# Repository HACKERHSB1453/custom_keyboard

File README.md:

# my-kkeb

A 113-key modular mechanical keyboard, split into 5 boards that connect with magnetic pogo pins. It is designed in KiCad (PCB) and Fusion (case) for Hack Club's KEEB program.

## Why I built it
I build this because I was interested in split keyboard. I really like how they look but I dont like how they sacrifice a lot of keys and thats makes them difficult to use for some things. So I had the idea to make a modular split keyboard. 
## How it works
The way it works it pretty simple. A pi pico powers it all. I used mcp23017 chips so I could get enough pins for all the matrix rows and colums from just transfering 4 pins thought the modules.
## Repository layout

```
my-kkeb/                 KiCad project (schematics + PCB)
  CUSTOM.pretty/         custom footprints (pogo connector, hot-swap socket, USB-C)
  export/fab/            Gerber zips, one per board, ready for JLCPCB
case/
  <Module>/Case_*.step   case for each module (one body per file for printing)
  <Module>/Plate_*.step  switch plate for each module
  my-kkeb-case-assembly.step   everything together, for viewing only
```

## Building it

1. **PCBs:** upload each zip from `my-kkeb/export/fab/` to JLCPCB as a separate order (5 boards).
2. **Case:** print the `Case_*` and `Plate_*` files from `case/`. I plan to use JLC3DP in black resin.
3. **Parts:** see `bom.csv`
4. **Firmware:** not done yet

## What I learned
I learned a lot of stuff. I learn a lot about how keyboard work. What I think that is the most valuable thing about what I learned is the knowladge about PCBs, I knew some stuff but I have never tried to actually make a PCB before. And it was actually harder than I thought for some things. But overall I enjoyed a lot doing everything. Making the case was definetely harder than doing the PCB, because I didnt really know how to make the it at first. I tried using FreeCad at first since fusion wasnt in linux, and I didnt liked onshape. But I ended up intalling fusion in my windows and Did 95% of they case there and a did some changed on freecad late on.

## Build journal

**Total: 80 hours**

| Date | Hours | What I worked on |
|---|---|---|
| August 3 | 1 h | Research |
| August 4 | – | GitHub repo |
| August 14 | 2 h 50 min | Planning and first 3D model |
| August 15 | 8 h 40 min | Main model, planning, OLED, pogo pins, MCP23017 |
| August 16 | 3 h | PCB |
| August 17 | 3 h 30 min | PCB |
| August 18 | 2 h | Model changes, PCB |
| August 19 | 9 h | Schematic, ERC |
| August 20 | 7 h | PCB placement |
| August 21 | 16 h | PCB placement and wiring |
| August 23 | 4 h | Wiring |
| August 28 | 6 h | Case |
| September 13 | 7 h | Case, rewiring |
| September 20 | 3 h | Case |
| September 25 | 7 h | Case |

### August 3 (1 h)
I have been searching about how keayboards work. And how matrix system works. Spend a total of 1 hour investigating and watching videos about how to keyboards work and how to create one. Here are the links:
- https://www.youtube.com/watch?v=8WXpGTIbxlQ
- https://www.youtube.com/watch?v=7LyziNdFlew
- https://www.youtube.com/watch?v=h-NM1xSSzHQ

### August 4
I created the github repo.

### August 14 (2 h 50 min)
- **2:10AM-3AM:** Planning my keyboard.
- **10PM-12AM:** I kept planning and making a 3D model to get an idea about how the keyboard should look like.

### August 15 (8 h 40 min)
- **12AM-3AM:** I finished the main model.

- **3AM-4:40AM:** I tought that I could add more things so I made the keyboard bigger. And also added attachable parts.

- **4:40AM-6AM:** I planned where everything will go. Searched about how to make the keyboard hotswappable. I had a problem and it is that the keyboard has 96 keys and 2 knobs. The pi pico doesnt have enough pins. I had two main options, use 2 pi picos or use a another chip. But after inverstigating I found ot a way to make it work with a single pi pico.
- **2PM-4PM:** I added an oled screen, installed kicad. And also searched about ways to connect the keyboard with magnets. I found out about pogo pins. And I decided using them.
- **11:20PM-12AM:** I searched about encoreds and searched about how a MCP23017 works and how to use it. I also watched this video about it

### August 16 (3 h)
- **12:20AM-1:50AM:** I created the kicad project and started adding the base thing like the swithes and the pi pico
- **8PM-11PM:** I started designing the pcb.
  - **8:15PM-9PM:** At this point i had the matrix of the right and left part, but it wasnt wired yet.

### August 17 (3 h 30 min)
- **12:30AM-1:40AM:** kept drawing the switch matrix: D30-D58 and their switches
- **3:20AM-3:50AM:** moved the whole matrix out of the main sheet into its own sheet called `left_part` and started using hierarchical schematic since it was for my case. I couldnt find much info online, but I managed to make it work
- **7:30PM-11PM:** I continued with the PCB, I accidentally forgot to save the right part the day before and had to redo that. I also started organizsing thingsa and connect the two main parts. I also search about mousebites. And I decided to use it since the keybaord will be split in multiple parts.

### August 18 (2 h)
- **4AM-4:10AM:** split `left_part` into two sheets, **Left** and **Right** (60 symbols each), and made an empty numpad sheet
- **2:30PM-3:30PM:** I made some changes to the keyboard model.

- **3PM-3:50PM:** filled the **Numpad** sheet: switches, diodes D59-D80 and its connector J3. Added SW2 to the Left sheet
- **11PM-12AM:** I continued with the pcb

### August 19 (9 h)
- **12AM-3AM:** I kept doing the pcb, and finished the connections. I tried to use schematic hiererchy to organize it all. I hope I didnt mess it up. In this period I basically added the Macro pad and the git pad. Here are some photos:
  - **12AM-1AM:** made the **Macro_pad** sheet (diodes D81-D96, connectors J5, J7, J8) and an empty Git_pad sheet
  - **2:25AM-3AM:** filled the **Git_pad** sheet (diodes D97-D112, connector J9)

- **3AM-7AM:** I fixed all the errors that didnt let me start the design of the PCB
  - **4:45AM-6:35AM:** first time the schematic was sent to the PCB editor: **247 footprints** appeared on the board. Replaced the old J1/J2 connectors with the two USB-C ports (J5 and J11)
- **10PM-12AM:** I run the ERC and got 74 errors. And I spend the time fixing them.
  - **11PM-11:40PM:** added labels on the Git_pad, Macro_pad, Numpad and Right sheets (the ERC fixing)

### August 20 (7 h)
- **12AM-5AM:** I started designing the PCB completed positioning the two main parts of the keybaord and also added the diodes to the left half. Here is a photo:
  - **12:45AM-4:50AM:** placed all 112 switches and the first 29 diodes on the Left board, and moved 31 parts to the back side. Removed an extra connector (J10)

- **10PM-12AM:** I continued with the PCB placement
  - **11PM-2:40AM:** placed all 112 diodes, the rest of the switches, the chips and the connectors (246 parts moved). Added the 113th key (MX113 and D113) to the Numpad

*(Postdata: I messed up really bad here, because I thought that the kailh sockets had to go on the front of the plate, I had to fix that late one)*

### August 21 (16 h)
- **12AM-5AM:** I finished the placement of the compenents in the PCB
- **10PM-12AM:** I continued started wiring the components
- **12AM-9AM:** I finished the wiring of the right part, left part. And the numpad.
  - **4:20AM-5:50AM:** first wiring: 553 track pieces and 87 vias
  - **7:15AM-9AM:** kept wigin and got up to **1,987 track pieces and 247 vias**

### August 23 (4 h)
- **12AM-4AM:** I finished wiring all the keybaord.
  - **1:20AM-5AM:** kept wiring and got from 1,987 to 2,514 track pieces, 324 vias
- **7:45PM-8:10PM:** restored a backup from KiCad's history, then kept wiring
- **9:45PM-10:30PM:** more wiring, up to **2,798 track pieces and 361 vias**

### August 24
- **2:30AM-3:30AM:** I added some ressistors and capacitators.

### August 28 (6 h)
- **12AM-6AM:** I started designing the case

### August 31
- **1:20AM-6:30AM:** I hadded mountholes to the pcb. Run DRC again, got a bunch of problems I solved the,

### September 13 (7 h)
- **12AM-2AM:** I kept designing the case
- **2AM-7AM:** I noticed that I had the kailh hotswap sockets in the wrong side of the board, so I had to basically rewire everything.

### September 20 (3 h)
- **3PM-6PM:** I kept designing everything, and finished the numpad.

### September 25 (7 h)
- **11AM-6PM:** I finished the full case, and seperated it into different files. Here are some photos:

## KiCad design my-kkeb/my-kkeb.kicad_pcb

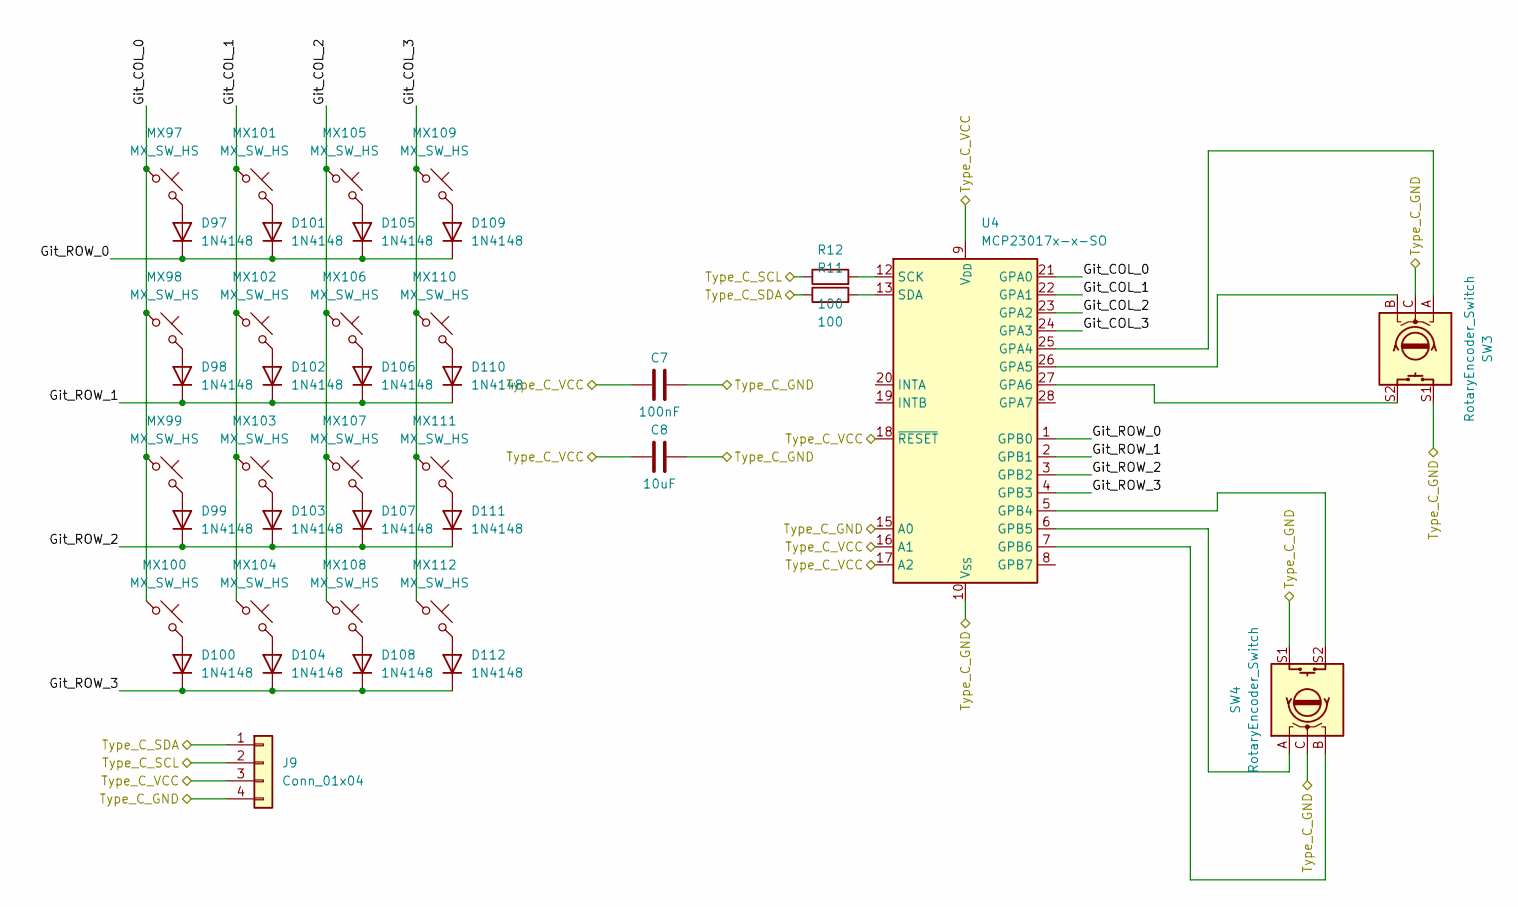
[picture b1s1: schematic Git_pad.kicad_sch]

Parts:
C7: 100nF; C_0603_1608Metric
C8: 10uF; C_0805_2012Metric
D97, D98, D99, D100, D101, D102, D103, D104, D105, D106, D107, D108, D109, D110, D111, D112: 1N4148; D_DO-35_SOD27_P7.62mm_Horizontal
J9: Conn_01x04; PogoMag_1x04_P2.54mm_RightAngle
MX97, MX98, MX99, MX100, MX101, MX102, MX103, MX104, MX105, MX106, MX107, MX108, MX109, MX110, MX111, MX112: MX_SW_HS; SW_MX_HS_CPG151101S11_1u_PinSwap
R11, R12: 100; R_0603_1608Metric
SW3, SW4: RotaryEncoder_Switch; ROT_Alps_EC11E-Switch
U4: MCP23017x-x-SO; SOIC-28W_7.5x17.9mm_P1.27mm

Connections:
/Git_pad/Git_COL_0: MX97.1 (2_2), MX98.1 (2_2), MX99.1 (2_2), MX100.1 (2_2), U4.21 (GPA0)
/Git_pad/Git_COL_1: MX101.1 (2_2), MX102.1 (2_2), MX103.1 (2_2), MX104.1 (2_2), U4.22 (GPA1)
/Git_pad/Git_COL_2: MX105.1 (2_2), MX106.1 (2_2), MX107.1 (2_2), MX108.1 (2_2), U4.23 (GPA2)
/Git_pad/Git_COL_3: MX109.1 (2_2), MX110.1 (2_2), MX111.1 (2_2), MX112.1 (2_2), U4.24 (GPA3)
/Git_pad/Git_ROW_0: D97.1 (K), D101.1 (K), D105.1 (K), D109.1 (K), U4.1 (GPB0)
/Git_pad/Git_ROW_1: D98.1 (K), D102.1 (K), D106.1 (K), D110.1 (K), U4.2 (GPB1)
/Git_pad/Git_ROW_2: D99.1 (K), D103.1 (K), D107.1 (K), D111.1 (K), U4.3 (GPB2)
/Git_pad/Git_ROW_3: D100.1 (K), D104.1 (K), D108.1 (K), D112.1 (K), U4.4 (GPB3)
/Git_pad/Type_C_GND: C7.2, C8.2, J9.4, SW3.C, SW3.S1, SW4.C, SW4.S1, U4.10 (V_{SS}), U4.15 (A0); also elsewhere on the board
/Git_pad/Type_C_SCL: J9.2, R12.1; also elsewhere on the board
/Git_pad/Type_C_SDA: J9.1, R11.1; also elsewhere on the board
/Git_pad/Type_C_VCC: C7.1, C8.1, J9.3, U4.9 (V_{DD}), U4.16 (A1), U4.17 (A2), U4.18 (~RESET); also elsewhere on the board
unnamed: D97.2 (A), MX97.2 (1_1)
unnamed: D98.2 (A), MX98.2 (1_1)
unnamed: D99.2 (A), MX99.2 (1_1)
unnamed: D100.2 (A), MX100.2 (1_1)
unnamed: D101.2 (A), MX101.2 (1_1)
unnamed: D102.2 (A), MX102.2 (1_1)
unnamed: D103.2 (A), MX103.2 (1_1)
unnamed: D104.2 (A), MX104.2 (1_1)
unnamed: D105.2 (A), MX105.2 (1_1)
unnamed: D106.2 (A), MX106.2 (1_1)
unnamed: D107.2 (A), MX107.2 (1_1)
unnamed: D108.2 (A), MX108.2 (1_1)
unnamed: D109.2 (A), MX109.2 (1_1)
unnamed: D110.2 (A), MX110.2 (1_1)
unnamed: D111.2 (A), MX111.2 (1_1)
unnamed: D112.2 (A), MX112.2 (1_1)
unnamed: SW3.A, U4.25 (GPA4)
unnamed: SW3.B, U4.26 (GPA5)
unnamed: SW3.S2, U4.27 (GPA6)
unnamed: SW4.S2, U4.5 (GPB4)
unnamed: SW4.A, U4.6 (GPB5)
unnamed: SW4.B, U4.7 (GPB6)
unnamed: R12.2, U4.12 (SCK)
unnamed: R11.2, U4.13 (SDA)

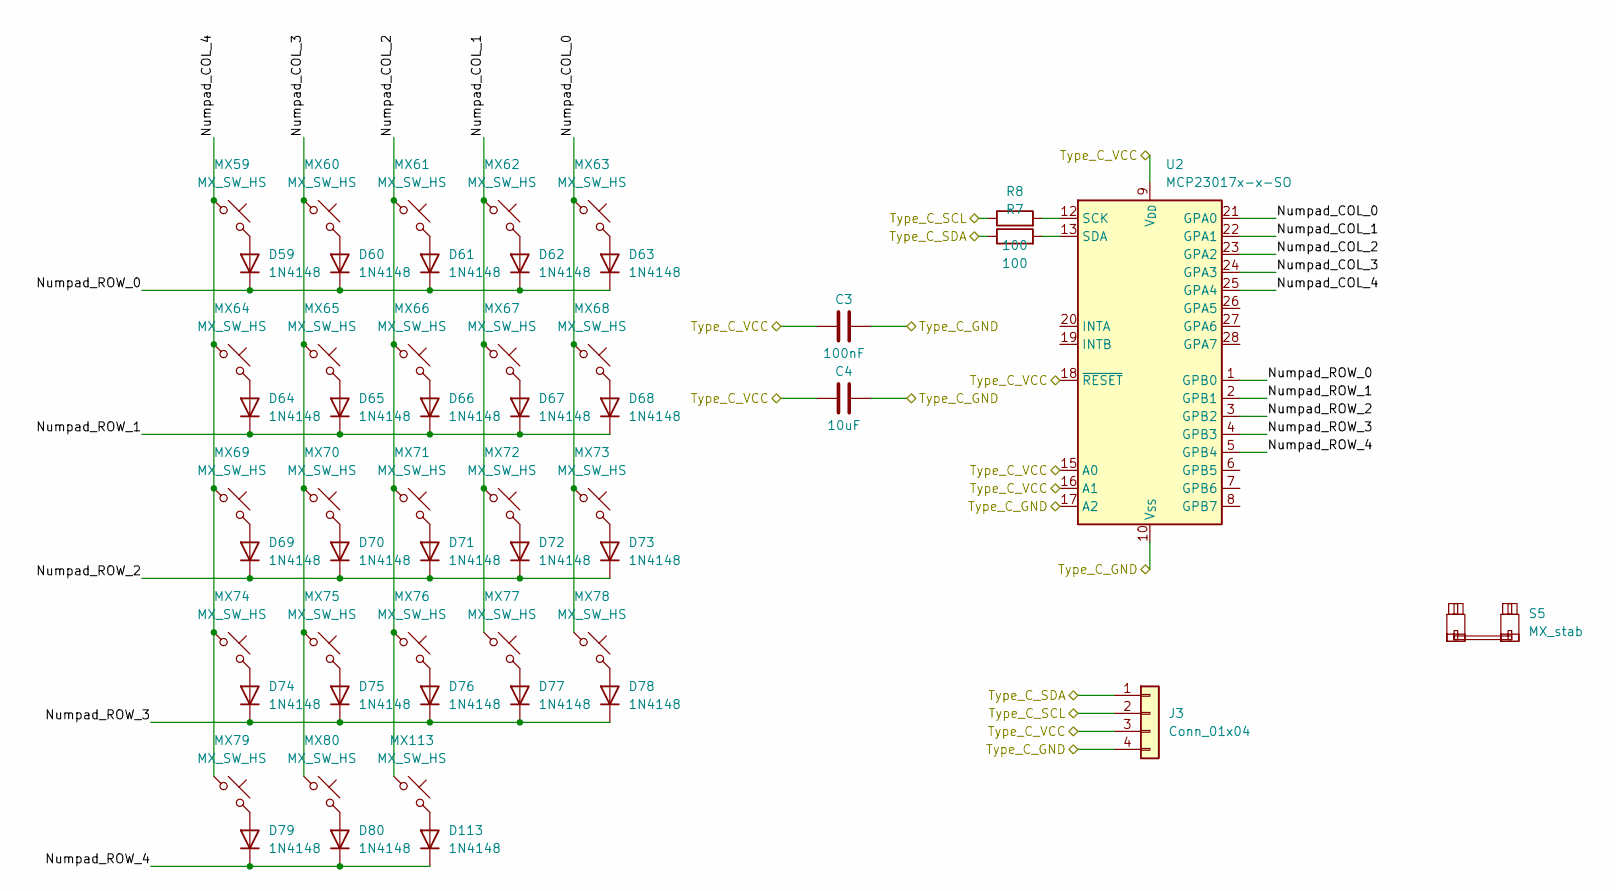
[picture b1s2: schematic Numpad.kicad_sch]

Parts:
C3: 100nF; C_0603_1608Metric
C4: 10uF; C_0805_2012Metric
D59, D60, D61, D62, D63, D64, D65, D66, D67, D68, D69, D70, D71, D72, D73, D74, D75, D76, D77, D78, D79, D80, D113: 1N4148; D_DO-35_SOD27_P7.62mm_Horizontal
J3: Conn_01x04; PogoMag_1x04_P2.54mm_RightAngle
MX59, MX60, MX61, MX62, MX63, MX64, MX65, MX66, MX67, MX68, MX69, MX70, MX71, MX72, MX73, MX74, MX75, MX76, MX77, MX78, MX79, MX80, MX113: MX_SW_HS; SW_MX_HS_CPG151101S11_1u_PinSwap
R7, R8: 100; R_0603_1608Metric
S5: MX_stab; STAB_MX_P_2u
U2: MCP23017x-x-SO; SOIC-28W_7.5x17.9mm_P1.27mm

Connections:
/Git_pad/Type_C_GND: C3.2, C4.2, J3.4, U2.10 (V_{SS}), U2.17 (A2); also elsewhere on the board
/Git_pad/Type_C_SCL: J3.2, R8.1; also elsewhere on the board
/Git_pad/Type_C_SDA: J3.1, R7.1; also elsewhere on the board
/Git_pad/Type_C_VCC: C3.1, C4.1, J3.3, U2.9 (V_{DD}), U2.15 (A0), U2.16 (A1), U2.18 (~RESET); also elsewhere on the board
/Numpad/Numpad_COL_0: MX63.1 (2_2), MX68.1 (2_2), MX73.1 (2_2), MX78.1 (2_2), U2.21 (GPA0)
/Numpad/Numpad_COL_1: MX62.1 (2_2), MX67.1 (2_2), MX72.1 (2_2), MX77.1 (2_2), U2.22 (GPA1)
/Numpad/Numpad_COL_2: MX61.1 (2_2), MX66.1 (2_2), MX71.1 (2_2), MX76.1 (2_2), MX113.1 (2_2), U2.23 (GPA2)
/Numpad/Numpad_COL_3: MX60.1 (2_2), MX65.1 (2_2), MX70.1 (2_2), MX75.1 (2_2), MX80.1 (2_2), U2.24 (GPA3)
/Numpad/Numpad_COL_4: MX59.1 (2_2), MX64.1 (2_2), MX69.1 (2_2), MX74.1 (2_2), MX79.1 (2_2), U2.25 (GPA4)
/Numpad/Numpad_ROW_0: D59.1 (K), D60.1 (K), D61.1 (K), D62.1 (K), D63.1 (K), U2.1 (GPB0)
/Numpad/Numpad_ROW_1: D64.1 (K), D65.1 (K), D66.1 (K), D67.1 (K), D68.1 (K), U2.2 (GPB1)
/Numpad/Numpad_ROW_2: D69.1 (K), D70.1 (K), D71.1 (K), D72.1 (K), D73.1 (K), U2.3 (GPB2)
/Numpad/Numpad_ROW_3: D74.1 (K), D75.1 (K), D76.1 (K), D77.1 (K), D78.1 (K), U2.4 (GPB3)
/Numpad/Numpad_ROW_4: D79.1 (K), D80.1 (K), D113.1 (K), U2.5 (GPB4)
unnamed: D59.2 (A), MX59.2 (1_1)
unnamed: D60.2 (A), MX60.2 (1_1)
unnamed: D61.2 (A), MX61.2 (1_1)
unnamed: D62.2 (A), MX62.2 (1_1)
unnamed: D63.2 (A), MX63.2 (1_1)
unnamed: D64.2 (A), MX64.2 (1_1)
unnamed: D65.2 (A), MX65.2 (1_1)
unnamed: D66.2 (A), MX66.2 (1_1)
unnamed: D67.2 (A), MX67.2 (1_1)
unnamed: D68.2 (A), MX68.2 (1_1)
unnamed: D69.2 (A), MX69.2 (1_1)
unnamed: D70.2 (A), MX70.2 (1_1)
unnamed: D71.2 (A), MX71.2 (1_1)
unnamed: D72.2 (A), MX72.2 (1_1)
unnamed: D73.2 (A), MX73.2 (1_1)
unnamed: D74.2 (A), MX74.2 (1_1)
unnamed: D75.2 (A), MX75.2 (1_1)
unnamed: D76.2 (A), MX76.2 (1_1)
unnamed: D77.2 (A), MX77.2 (1_1)
unnamed: D78.2 (A), MX78.2 (1_1)
unnamed: D79.2 (A), MX79.2 (1_1)
unnamed: D80.2 (A), MX80.2 (1_1)
unnamed: D113.2 (A), MX113.2 (1_1)
unnamed: R8.2, U2.12 (SCK)
unnamed: R7.2, U2.13 (SDA)

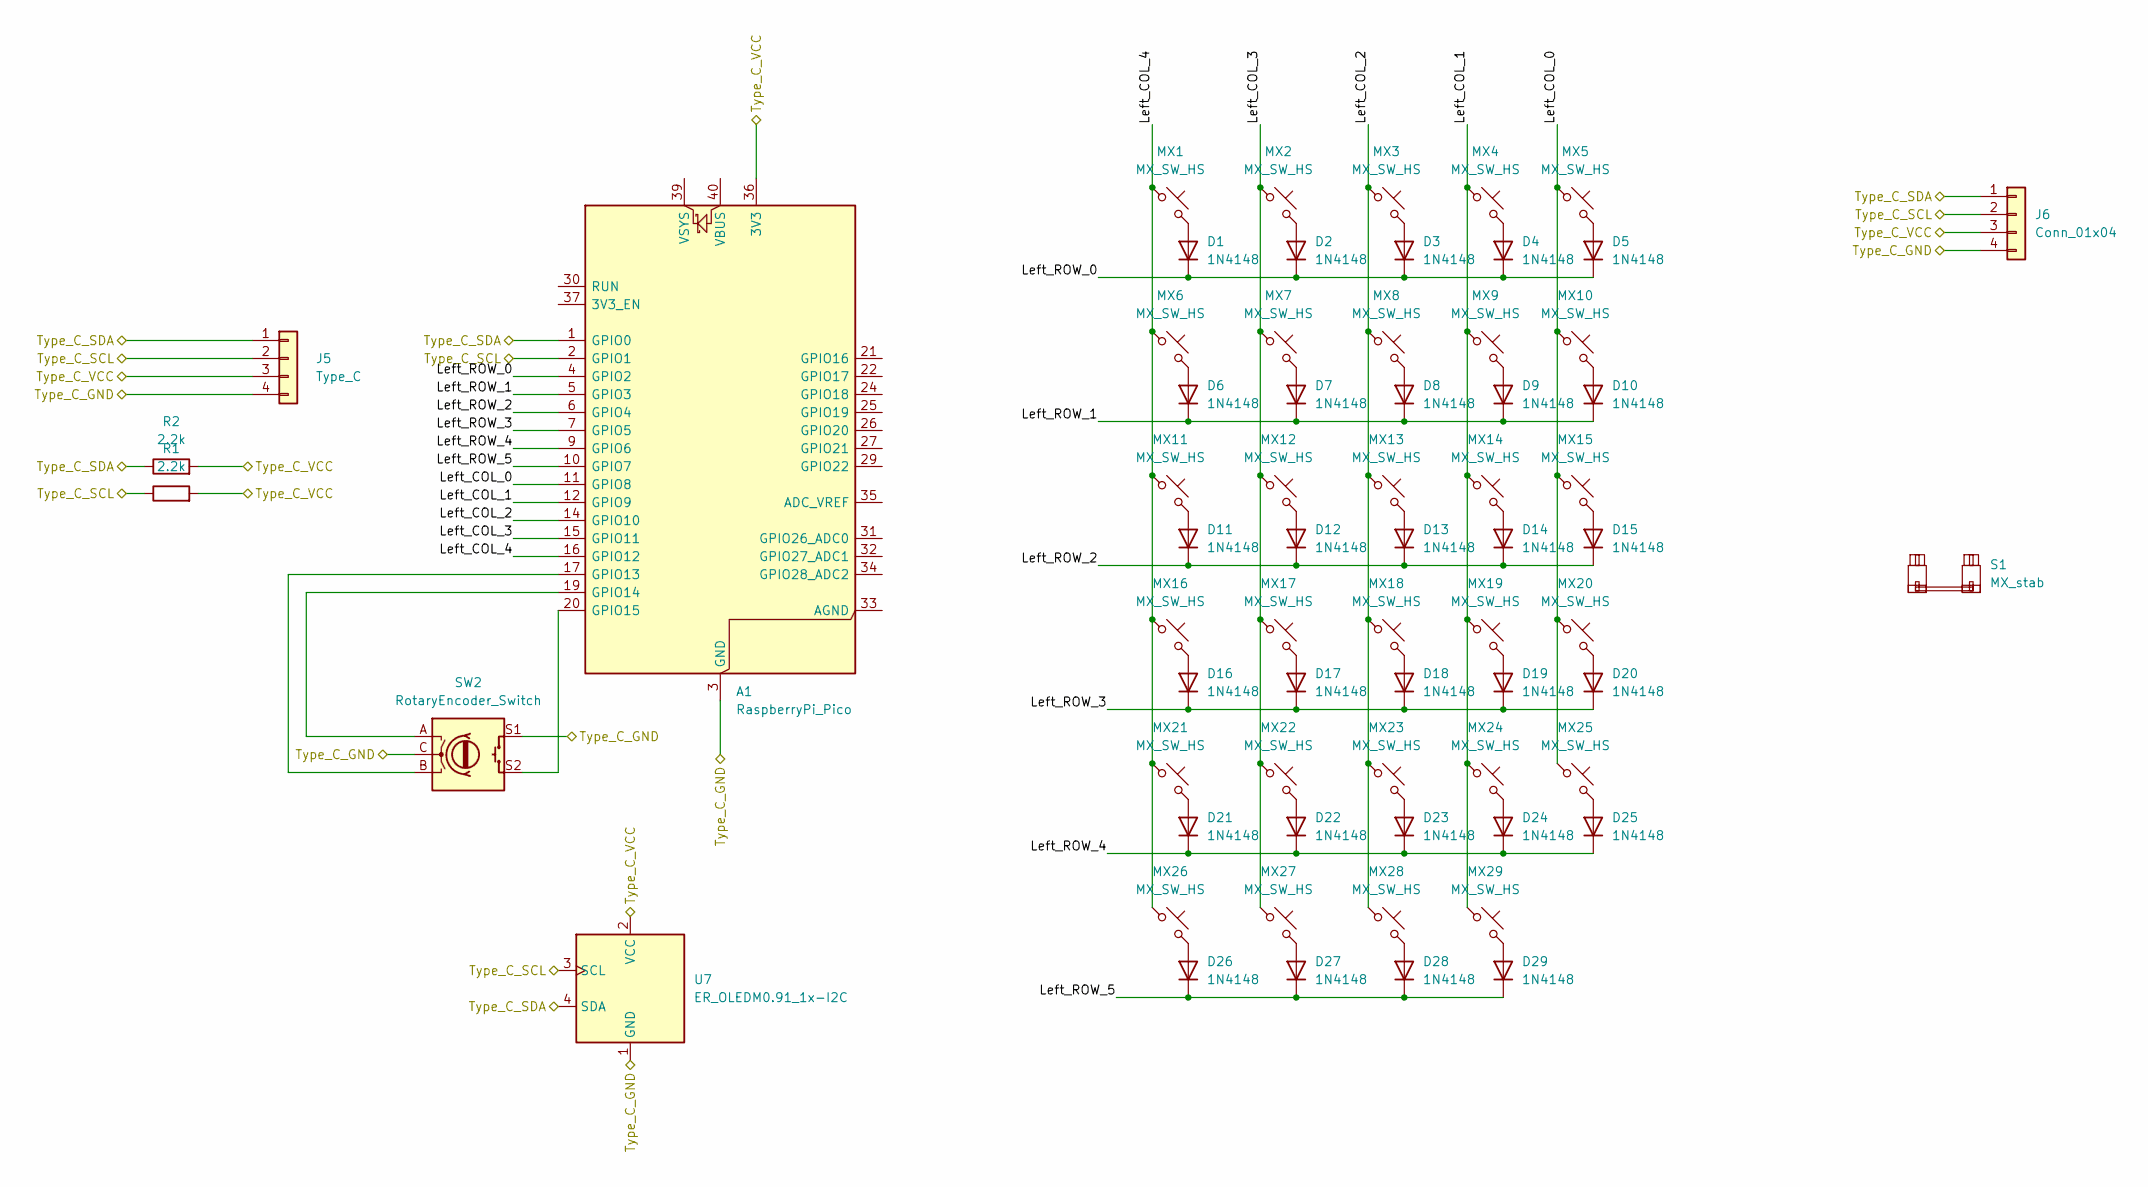
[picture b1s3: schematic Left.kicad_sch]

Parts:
A1: RaspberryPi_Pico; RaspberryPi_Pico_Common_Unspecified
D1, D2, D3, D4, D5, D6, D7, D8, D9, D10, D11, D12, D13, D14, D15, D16, D17, D18, D19, D20, D21, D22, D23, D24, D25, D26, D27, D28, D29: 1N4148; D_DO-35_SOD27_P7.62mm_Horizontal
J5: Type_C; USB_C_Receptacle_HRO_TYPE-C-31-M-12_4Pin_Fixed
J6: Conn_01x04; PogoMag_1x04_P2.54mm_RightAngle
MX1, MX2, MX3, MX4, MX5, MX6, MX7, MX8, MX9, MX10, MX11, MX12, MX13, MX14, MX15, MX16, MX17, MX18, MX19, MX20, MX21, MX22, MX23, MX24, MX25, MX26, MX27, MX28, MX29: MX_SW_HS; SW_MX_HS_CPG151101S11_1u_PinSwap
R1, R2: 2.2k; R_0603_1608Metric
S1: MX_stab; STAB_MX_P_2u
SW2: RotaryEncoder_Switch; ROT_Alps_EC11E-Switch
U7: ER_OLEDM0.91_1x-I2C

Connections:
/Git_pad/Type_C_GND: A1.3 (GND), A1.8 (GND), A1.13 (GND), A1.18 (GND), A1.23 (GND), A1.28 (GND), A1.38 (GND), J5.4, J6.4, SW2.C, SW2.S1, U7.1 (GND); also elsewhere on the board
/Git_pad/Type_C_SCL: A1.2 (GPIO1), J5.2, J6.2, R1.1, U7.3 (SCL); also elsewhere on the board
/Git_pad/Type_C_SDA: A1.1 (GPIO0), J5.1, J6.1, R2.1, U7.4 (SDA); also elsewhere on the board
/Git_pad/Type_C_VCC: A1.36 (3V3), J5.3, J6.3, R1.2, R2.2, U7.2 (VCC); also elsewhere on the board
/Left/Left_COL_0: A1.11 (GPIO8), MX5.1 (2_2), MX10.1 (2_2), MX15.1 (2_2), MX20.1 (2_2), MX25.1 (2_2)
/Left/Left_COL_1: A1.12 (GPIO9), MX4.1 (2_2), MX9.1 (2_2), MX14.1 (2_2), MX19.1 (2_2), MX24.1 (2_2), MX29.1 (2_2)
/Left/Left_COL_2: A1.14 (GPIO10), MX3.1 (2_2), MX8.1 (2_2), MX13.1 (2_2), MX18.1 (2_2), MX23.1 (2_2), MX28.1 (2_2)
/Left/Left_COL_3: A1.15 (GPIO11), MX2.1 (2_2), MX7.1 (2_2), MX12.1 (2_2), MX17.1 (2_2), MX22.1 (2_2), MX27.1 (2_2)
/Left/Left_COL_4: A1.16 (GPIO12), MX1.1 (2_2), MX6.1 (2_2), MX11.1 (2_2), MX16.1 (2_2), MX21.1 (2_2), MX26.1 (2_2)
/Left/Left_ROW_0: A1.4 (GPIO2), D1.1 (K), D2.1 (K), D3.1 (K), D4.1 (K), D5.1 (K)
/Left/Left_ROW_1: A1.5 (GPIO3), D6.1 (K), D7.1 (K), D8.1 (K), D9.1 (K), D10.1 (K)
/Left/Left_ROW_2: A1.6 (GPIO4), D11.1 (K), D12.1 (K), D13.1 (K), D14.1 (K), D15.1 (K)
/Left/Left_ROW_3: A1.7 (GPIO5), D16.1 (K), D17.1 (K), D18.1 (K), D19.1 (K), D20.1 (K)
/Left/Left_ROW_4: A1.9 (GPIO6), D21.1 (K), D22.1 (K), D23.1 (K), D24.1 (K), D25.1 (K)
/Left/Left_ROW_5: A1.10 (GPIO7), D26.1 (K), D27.1 (K), D28.1 (K), D29.1 (K)
unnamed: A1.17 (GPIO13), SW2.B
unnamed: A1.19 (GPIO14), SW2.A
unnamed: A1.20 (GPIO15), SW2.S2
unnamed: D1.2 (A), MX1.2 (1_1)
unnamed: D2.2 (A), MX2.2 (1_1)
unnamed: D3.2 (A), MX3.2 (1_1)
unnamed: D4.2 (A), MX4.2 (1_1)
unnamed: D5.2 (A), MX5.2 (1_1)
unnamed: D6.2 (A), MX6.2 (1_1)
unnamed: D7.2 (A), MX7.2 (1_1)
unnamed: D8.2 (A), MX8.2 (1_1)
unnamed: D9.2 (A), MX9.2 (1_1)
unnamed: D10.2 (A), MX10.2 (1_1)
unnamed: D11.2 (A), MX11.2 (1_1)
unnamed: D12.2 (A), MX12.2 (1_1)
unnamed: D13.2 (A), MX13.2 (1_1)
unnamed: D14.2 (A), MX14.2 (1_1)
unnamed: D15.2 (A), MX15.2 (1_1)
unnamed: D16.2 (A), MX16.2 (1_1)
unnamed: D17.2 (A), MX17.2 (1_1)
unnamed: D18.2 (A), MX18.2 (1_1)
unnamed: D19.2 (A), MX19.2 (1_1)
unnamed: D20.2 (A), MX20.2 (1_1)
unnamed: D21.2 (A), MX21.2 (1_1)
unnamed: D22.2 (A), MX22.2 (1_1)
unnamed: D23.2 (A), MX23.2 (1_1)
unnamed: D24.2 (A), MX24.2 (1_1)
unnamed: D25.2 (A), MX25.2 (1_1)
unnamed: D26.2 (A), MX26.2 (1_1)
unnamed: D27.2 (A), MX27.2 (1_1)
unnamed: D28.2 (A), MX28.2 (1_1)
unnamed: D29.2 (A), MX29.2 (1_1)

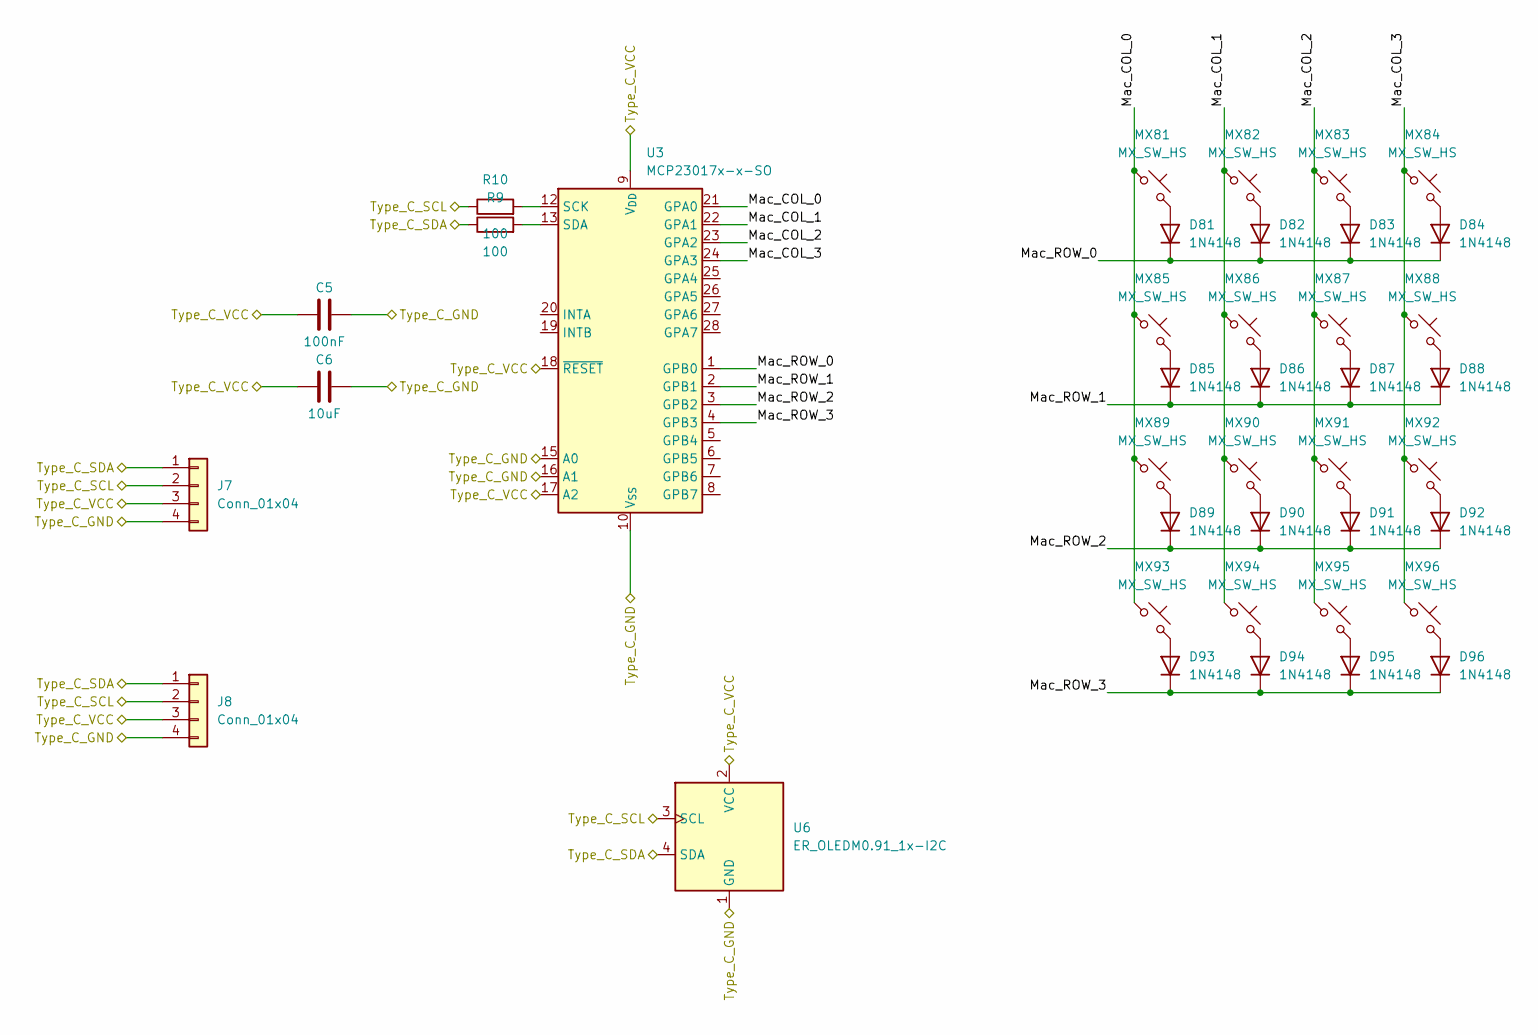
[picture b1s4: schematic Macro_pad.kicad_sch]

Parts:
C5: 100nF; C_0603_1608Metric
C6: 10uF; C_0805_2012Metric
D81, D82, D83, D84, D85, D86, D87, D88, D89, D90, D91, D92, D93, D94, D95, D96: 1N4148; D_DO-35_SOD27_P7.62mm_Horizontal
J7, J8: Conn_01x04; PogoMag_1x04_P2.54mm_RightAngle
MX81, MX82, MX83, MX84, MX85, MX86, MX87, MX88, MX89, MX90, MX91, MX92, MX93, MX94, MX95, MX96: MX_SW_HS; SW_MX_HS_CPG151101S11_1u_PinSwap
R9, R10: 100; R_0603_1608Metric
U3: MCP23017x-x-SO; SOIC-28W_7.5x17.9mm_P1.27mm
U6: ER_OLEDM0.91_1x-I2C

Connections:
/Git_pad/Type_C_GND: C5.2, C6.2, J7.4, J8.4, U3.10 (V_{SS}), U3.15 (A0), U3.16 (A1), U6.1 (GND); also elsewhere on the board
/Git_pad/Type_C_SCL: J7.2, J8.2, R10.1, U6.3 (SCL); also elsewhere on the board
/Git_pad/Type_C_SDA: J7.1, J8.1, R9.1, U6.4 (SDA); also elsewhere on the board
/Git_pad/Type_C_VCC: C5.1, C6.1, J7.3, J8.3, U3.9 (V_{DD}), U3.17 (A2), U3.18 (~RESET), U6.2 (VCC); also elsewhere on the board
/Macro_pad/Mac_COL_0: MX81.1 (2_2), MX85.1 (2_2), MX89.1 (2_2), MX93.1 (2_2), U3.21 (GPA0)
/Macro_pad/Mac_COL_1: MX82.1 (2_2), MX86.1 (2_2), MX90.1 (2_2), MX94.1 (2_2), U3.22 (GPA1)
/Macro_pad/Mac_COL_2: MX83.1 (2_2), MX87.1 (2_2), MX91.1 (2_2), MX95.1 (2_2), U3.23 (GPA2)
/Macro_pad/Mac_COL_3: MX84.1 (2_2), MX88.1 (2_2), MX92.1 (2_2), MX96.1 (2_2), U3.24 (GPA3)
/Macro_pad/Mac_ROW_0: D81.1 (K), D82.1 (K), D83.1 (K), D84.1 (K), U3.1 (GPB0)
/Macro_pad/Mac_ROW_1: D85.1 (K), D86.1 (K), D87.1 (K), D88.1 (K), U3.2 (GPB1)
/Macro_pad/Mac_ROW_2: D89.1 (K), D90.1 (K), D91.1 (K), D92.1 (K), U3.3 (GPB2)
/Macro_pad/Mac_ROW_3: D93.1 (K), D94.1 (K), D95.1 (K), D96.1 (K), U3.4 (GPB3)
unnamed: D81.2 (A), MX81.2 (1_1)
unnamed: D82.2 (A), MX82.2 (1_1)
unnamed: D83.2 (A), MX83.2 (1_1)
unnamed: D84.2 (A), MX84.2 (1_1)
unnamed: D85.2 (A), MX85.2 (1_1)
unnamed: D86.2 (A), MX86.2 (1_1)
unnamed: D87.2 (A), MX87.2 (1_1)
unnamed: D88.2 (A), MX88.2 (1_1)
unnamed: D89.2 (A), MX89.2 (1_1)
unnamed: D90.2 (A), MX90.2 (1_1)
unnamed: D91.2 (A), MX91.2 (1_1)
unnamed: D92.2 (A), MX92.2 (1_1)
unnamed: D93.2 (A), MX93.2 (1_1)
unnamed: D94.2 (A), MX94.2 (1_1)
unnamed: D95.2 (A), MX95.2 (1_1)
unnamed: D96.2 (A), MX96.2 (1_1)
unnamed: R10.2, U3.12 (SCK)
unnamed: R9.2, U3.13 (SDA)

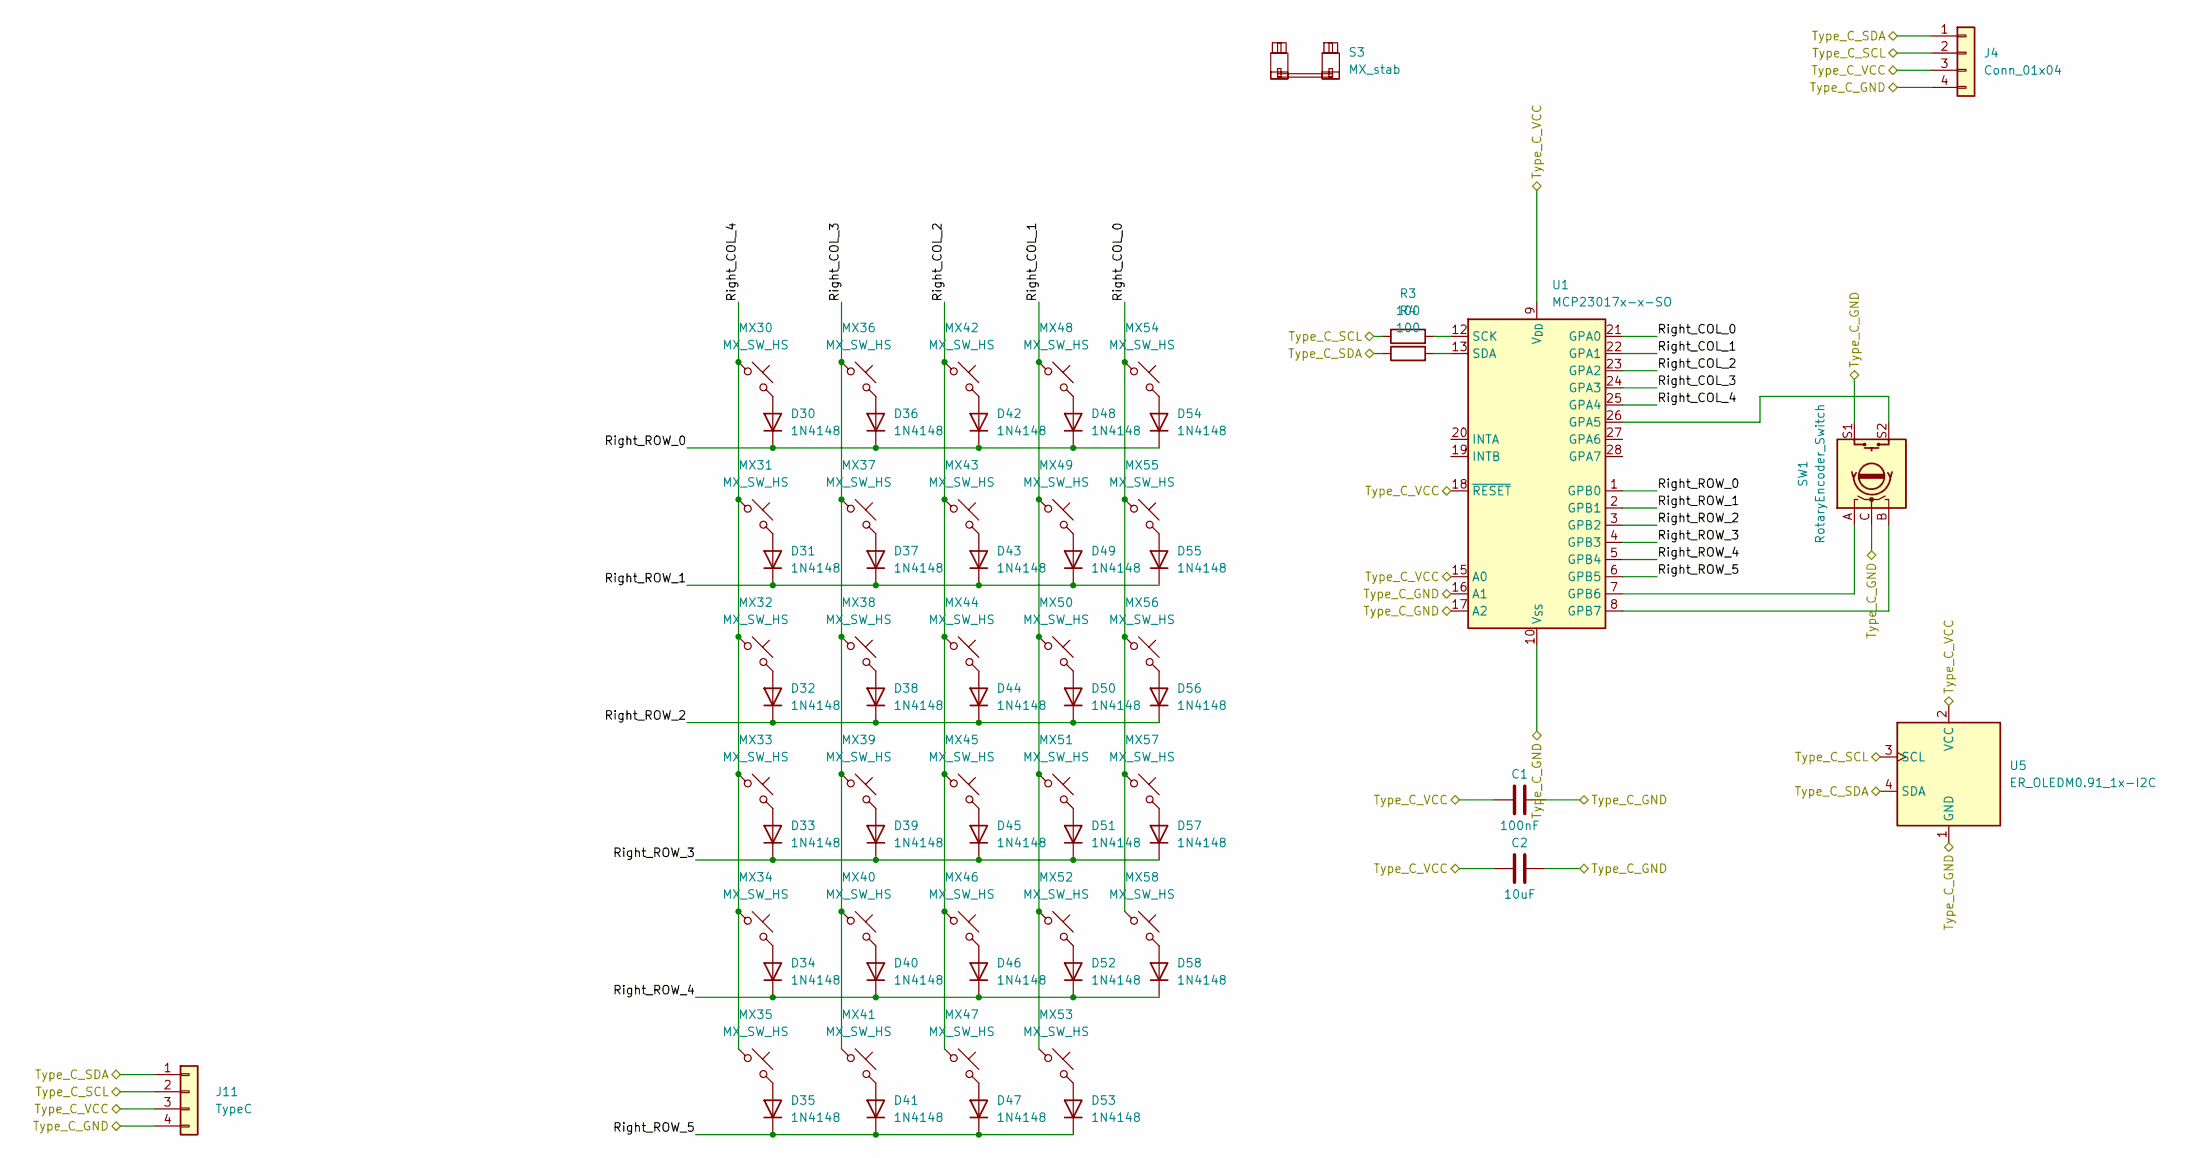
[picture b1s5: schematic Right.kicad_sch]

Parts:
C1: 100nF; C_0603_1608Metric
C2: 10uF; C_0805_2012Metric
D30, D31, D32, D33, D34, D35, D36, D37, D38, D39, D40, D41, D42, D43, D44, D45, D46, D47, D48, D49, D50, D51, D52, D53, D54, D55, D56, D57, D58: 1N4148; D_DO-35_SOD27_P7.62mm_Horizontal
J4: Conn_01x04; PogoMag_1x04_P2.54mm_RightAngle
J11: TypeC; USB_C_Receptacle_HRO_TYPE-C-31-M-12_4Pin_Fixed
MX30, MX31, MX32, MX33, MX34, MX35, MX36, MX37, MX38, MX39, MX40, MX41, MX42, MX43, MX44, MX45, MX46, MX47, MX48, MX49, MX50, MX51, MX52, MX53, MX54, MX55, MX56, MX57, MX58: MX_SW_HS; SW_MX_HS_CPG151101S11_1u_PinSwap
R3, R4: 100; R_0603_1608Metric
S3: MX_stab; STAB_MX_P_2u
SW1: RotaryEncoder_Switch; ROT_Alps_EC11E-Switch
U1: MCP23017x-x-SO; SOIC-28W_7.5x17.9mm_P1.27mm
U5: ER_OLEDM0.91_1x-I2C

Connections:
/Git_pad/Type_C_GND: C1.2, C2.2, J4.4, J11.4, SW1.C, SW1.S1, U1.10 (V_{SS}), U1.16 (A1), U1.17 (A2), U5.1 (GND); also elsewhere on the board
/Git_pad/Type_C_SCL: J4.2, J11.2, R3.1, U5.3 (SCL); also elsewhere on the board
/Git_pad/Type_C_SDA: J4.1, J11.1, R4.1, U5.4 (SDA); also elsewhere on the board
/Git_pad/Type_C_VCC: C1.1, C2.1, J4.3, J11.3, U1.9 (V_{DD}), U1.15 (A0), U1.18 (~RESET), U5.2 (VCC); also elsewhere on the board
/Right/Right_COL_0: MX54.1 (2_2), MX55.1 (2_2), MX56.1 (2_2), MX57.1 (2_2), MX58.1 (2_2), U1.21 (GPA0)
/Right/Right_COL_1: MX48.1 (2_2), MX49.1 (2_2), MX50.1 (2_2), MX51.1 (2_2), MX52.1 (2_2), MX53.1 (2_2), U1.22 (GPA1)
/Right/Right_COL_2: MX42.1 (2_2), MX43.1 (2_2), MX44.1 (2_2), MX45.1 (2_2), MX46.1 (2_2), MX47.1 (2_2), U1.23 (GPA2)
/Right/Right_COL_3: MX36.1 (2_2), MX37.1 (2_2), MX38.1 (2_2), MX39.1 (2_2), MX40.1 (2_2), MX41.1 (2_2), U1.24 (GPA3)
/Right/Right_COL_4: MX30.1 (2_2), MX31.1 (2_2), MX32.1 (2_2), MX33.1 (2_2), MX34.1 (2_2), MX35.1 (2_2), U1.25 (GPA4)
/Right/Right_ROW_0: D30.1 (K), D36.1 (K), D42.1 (K), D48.1 (K), D54.1 (K), U1.1 (GPB0)
/Right/Right_ROW_1: D31.1 (K), D37.1 (K), D43.1 (K), D49.1 (K), D55.1 (K), U1.2 (GPB1)
/Right/Right_ROW_2: D32.1 (K), D38.1 (K), D44.1 (K), D50.1 (K), D56.1 (K), U1.3 (GPB2)
/Right/Right_ROW_3: D33.1 (K), D39.1 (K), D45.1 (K), D51.1 (K), D57.1 (K), U1.4 (GPB3)
/Right/Right_ROW_4: D34.1 (K), D40.1 (K), D46.1 (K), D52.1 (K), D58.1 (K), U1.5 (GPB4)
/Right/Right_ROW_5: D35.1 (K), D41.1 (K), D47.1 (K), D53.1 (K), U1.6 (GPB5)
unnamed: D30.2 (A), MX30.2 (1_1)
unnamed: D31.2 (A), MX31.2 (1_1)
unnamed: D32.2 (A), MX32.2 (1_1)
unnamed: D33.2 (A), MX33.2 (1_1)
unnamed: D34.2 (A), MX34.2 (1_1)
unnamed: D35.2 (A), MX35.2 (1_1)
unnamed: D36.2 (A), MX36.2 (1_1)
unnamed: D37.2 (A), MX37.2 (1_1)
unnamed: D38.2 (A), MX38.2 (1_1)
unnamed: D39.2 (A), MX39.2 (1_1)
unnamed: D40.2 (A), MX40.2 (1_1)
unnamed: D41.2 (A), MX41.2 (1_1)
unnamed: D42.2 (A), MX42.2 (1_1)
unnamed: D43.2 (A), MX43.2 (1_1)
unnamed: D44.2 (A), MX44.2 (1_1)
unnamed: D45.2 (A), MX45.2 (1_1)
unnamed: D46.2 (A), MX46.2 (1_1)
unnamed: D47.2 (A), MX47.2 (1_1)
unnamed: D48.2 (A), MX48.2 (1_1)
unnamed: D49.2 (A), MX49.2 (1_1)
unnamed: D50.2 (A), MX50.2 (1_1)
unnamed: D51.2 (A), MX51.2 (1_1)
unnamed: D52.2 (A), MX52.2 (1_1)
unnamed: D53.2 (A), MX53.2 (1_1)
unnamed: D54.2 (A), MX54.2 (1_1)
unnamed: D55.2 (A), MX55.2 (1_1)
unnamed: D56.2 (A), MX56.2 (1_1)
unnamed: D57.2 (A), MX57.2 (1_1)
unnamed: D58.2 (A), MX58.2 (1_1)
unnamed: SW1.S2, U1.26 (GPA5)
unnamed: SW1.A, U1.7 (GPB6)
unnamed: SW1.B, U1.8 (GPB7)
unnamed: R3.2, U1.12 (SCK)
unnamed: R4.2, U1.13 (SDA)

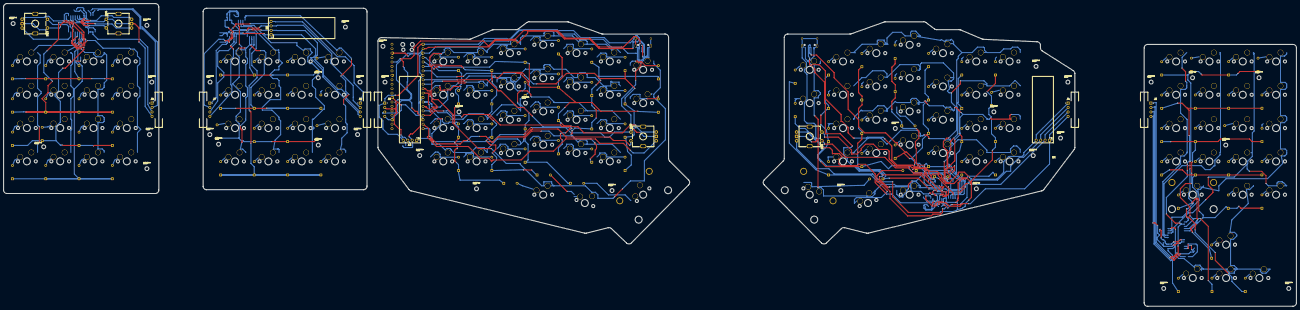
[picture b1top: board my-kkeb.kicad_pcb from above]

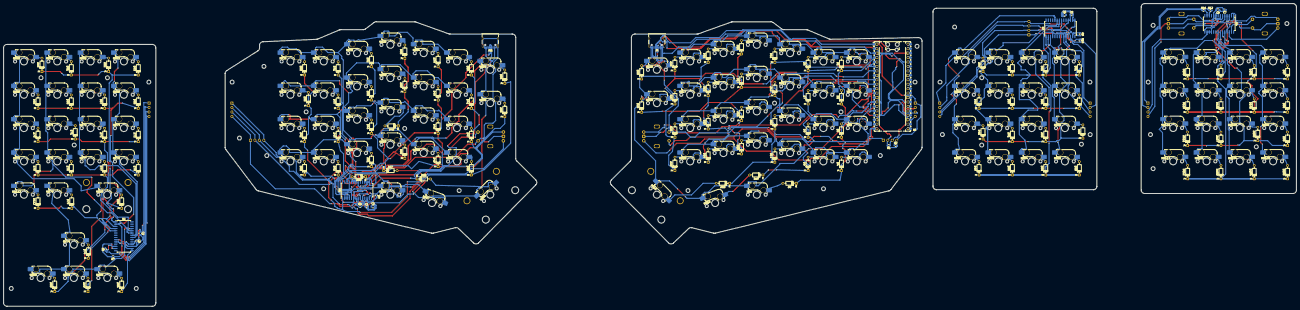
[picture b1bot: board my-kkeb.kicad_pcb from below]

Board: 2 copper layers, 739.3 x 173.1 mm, 267 parts (251 on the bottom side), 185 nets.
